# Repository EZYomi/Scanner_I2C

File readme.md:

# Mini Projet Scanner I2C

### Réalisé par mes soins 📌

Dans ce répertoire vous trouverez mes différents ficher de PCB ainsi que que de codage en langage C adapté Arduino. 

#### Matériel Utilisé 🧰

| Nom  🏷️    | Description 📖 |
| ----------- | ----------- |
| [LCD Hitachi](https://www.alldatasheet.com/datasheet-pdf/pdf/63673/HITACHI/HD44780.html)      | Ecran LCD en I2C       |
| [Beginner Kit Grove](https://www.gotronic.fr/art-beginner-kit-grove-110061162-31759.htm)      | Beginner Kit Grove de Seeedstudio spécialement prévu pour le monde de l'éducation proposant 12 projets Arduino reposants sur 10 modules Grove.       |
| [Broche Pogo](https://www.amazon.fr/Connecteurs-%C3%A9lectriques-Industriels-%C3%A9lectronique-Automobile/dp/B0F9LC9N87/ref=sr_1_18_sspa?__mk_fr_FR=%C3%85M%C3%85%C5%BD%C3%95%C3%91&crid=3KOYI9NY5HROW&dib=eyJ2IjoiMSJ9.8agn-p5RU884GjmctHngVaw38WZ8QR_x19pRdE1nuCrHeSdvz4q5IwNY3RV67dovoLLWUoWPLOadWBapfy3xcv7TXvfdvYMzYT3YVmWDnaX8qZfVgV1Zi2P-v6lGEjXEtML1IxxYgfLoKAuZ2CPc_V95-OBpd-mmGAkokWG-ELojFpAKphBq2-IrJhT4wf811Pz9_4ANHTz2h0NharQUT2y0uVdjxz91WWGvPjFvyl7G6qNUA6HCWjMKs9LSrpubqwIRaz7f5q0FzqJ6RuAYgDHNuwXUS2lEImtChZe6Hvo.dxwsfJOrP5SxurNdvKnmHxaJozR2LFn7prHrE1S2rZw&dib_tag=se&keywords=broche+pogo&qid=1790951161&sprefix=broche+pogo%2Caps%2C1325&sr=8-18-spons&aref=wVf9xaEqUO&sp_csd=d2lkZ2V0TmFtZT1zcF9tdGY&psc=1)      | Connecteur Facile d'utilisation      |
| [Liquid Crystal](https://docs.arduino.cc/libraries/liquidcrystal/)      | Bibliothèque Arduino. Cette bibliothèque permet à une carte Arduino/Genuino de contrôler des écrans LCD basés sur le chipset Hitachi HD44780 (ou compatible), présent dans la plupart des écrans LCD à affichage texte. Elle fonctionne en mode 4 ou 8 bits (c'est-à-dire en utilisant 4 ou 8 lignes de données en plus des lignes rs, enable et, éventuellement, rw de contrôle).       |

#### Feuille de route 🗃️

- [x] Imagination et conception du schéma et du PCB
- [] Programmer en Langage C / Arduino
- [] Prévoir une procédure de test complète
- [] Versionnage du projet a l'aide de GIT
- [] Création d'un README esthéthique et mise à jour

Pour plus d'information vous pouvez me contacter. [📑](https://mail.google.com/mail/u/0/?service=mail&flowName=GlifWebSignIn&flowEntry=AccountChooser&ec=asw-gmail-globalnav-signin#inbox?compose=new)

#### Merci d'avoir pris connaissance de ce répertoire traitant de mon Mini Projet

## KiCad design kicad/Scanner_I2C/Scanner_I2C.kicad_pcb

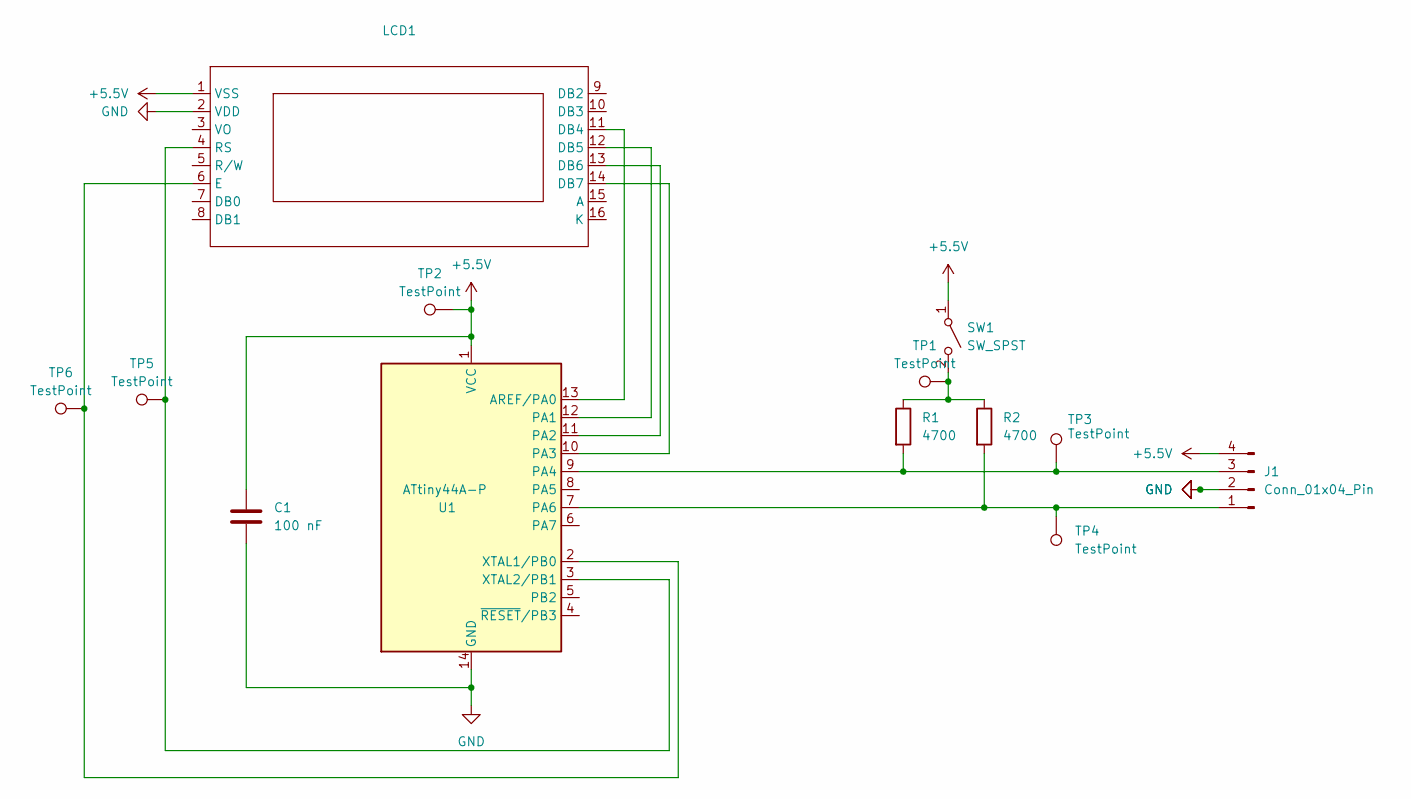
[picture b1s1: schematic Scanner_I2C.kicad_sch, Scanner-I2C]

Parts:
C1: 100 nF; C_Axial_L3.8mm_D2.6mm_P7.50mm_Horizontal
J1: Conn_01x04_Pin; PinHeader_1x04_P1.27mm_Vertical
LCD1: LCD
R1, R2: 4700; R_Axial_DIN0204_L3.6mm_D1.6mm_P7.62mm_Horizontal
SW1: SW_SPST; SW_DIP_SPSTx01_Slide_6.7x4.1mm_W7.62mm_P2.54mm_LowProfile
TP1, TP2, TP3, TP4, TP5, TP6: TestPoint; PinHeader_1x01_P1.00mm_Vertical
U1: ATtiny44A-P; DIP-14_W7.62mm

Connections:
+5.5V: C1.1, J1.4, LCD1.1 (VSS), SW1.1 (A), TP2.1, U1.1 (VCC)
GND: C1.2, J1.2, LCD1.2 (VDD), U1.14 (GND)
unnamed: J1.1, R2.2, TP4.1, U1.7 (PA6)
unnamed: J1.3, R1.2, TP3.1, U1.9 (PA4)
unnamed: LCD1.11 (DB4), U1.13 (AREF/PA0)
unnamed: LCD1.12 (DB5), U1.12 (PA1)
unnamed: LCD1.13 (DB6), U1.11 (PA2)
unnamed: LCD1.14 (DB7), U1.10 (PA3)
unnamed: LCD1.6 (E), TP6.1, U1.2 (XTAL1/PB0)
unnamed: LCD1.4 (RS), TP5.1, U1.3 (XTAL2/PB1)
unnamed: R1.1, R2.1, SW1.2 (B), TP1.1

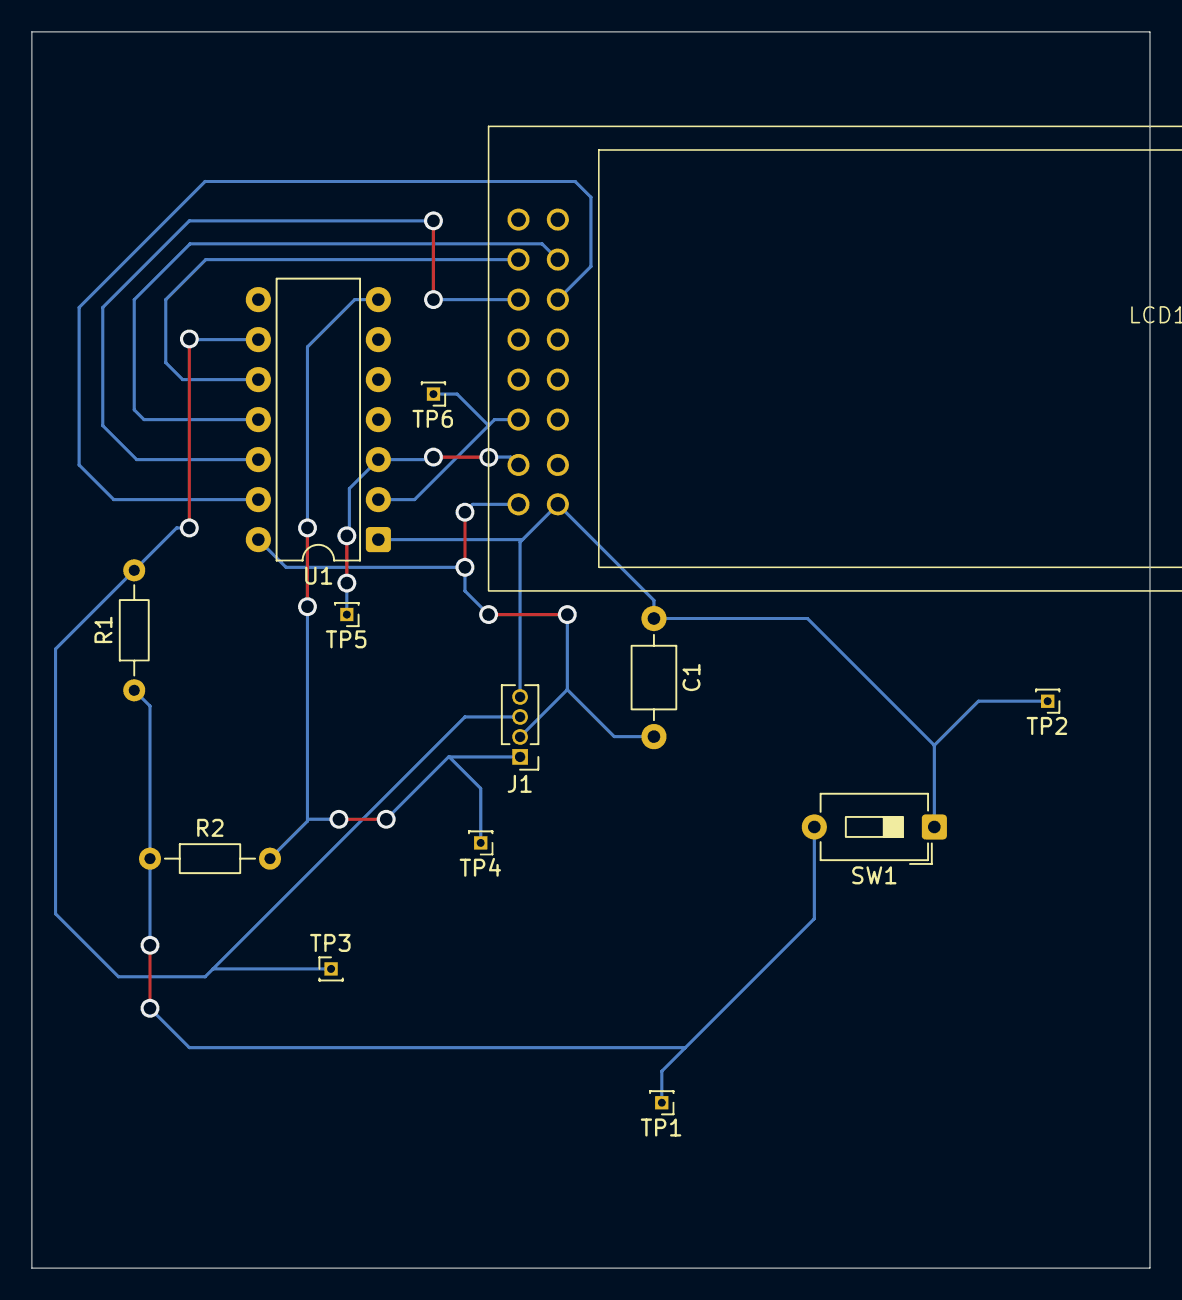
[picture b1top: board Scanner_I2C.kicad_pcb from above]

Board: 2 copper layers, 71.0 x 78.5 mm, 13 parts (0 on the bottom side), 11 nets.
